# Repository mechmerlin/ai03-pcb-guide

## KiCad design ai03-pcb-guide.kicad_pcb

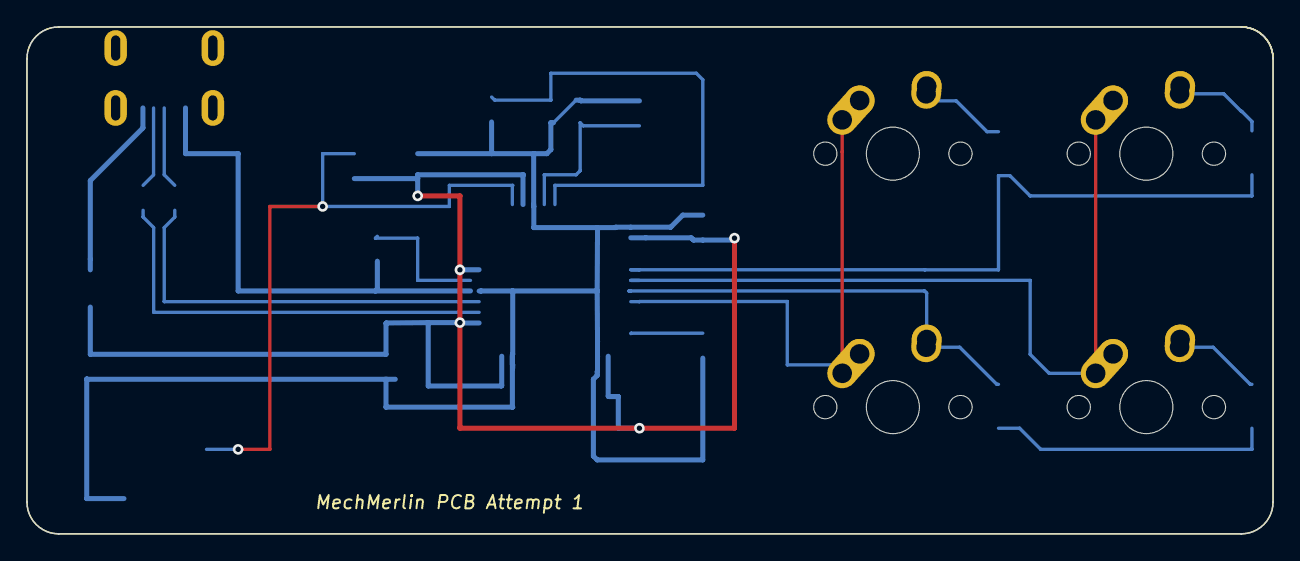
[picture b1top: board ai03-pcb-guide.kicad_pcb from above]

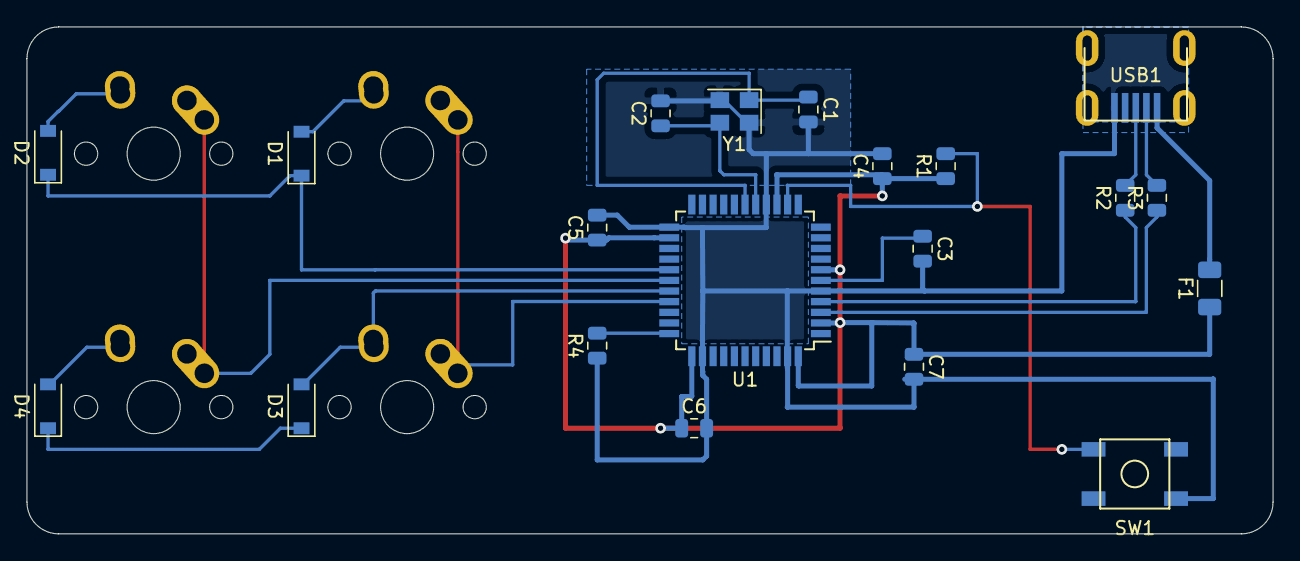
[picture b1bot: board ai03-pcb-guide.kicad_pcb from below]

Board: 2 copper layers, 93.7 x 38.1 mm, 24 parts (20 on the bottom side), 20 nets.

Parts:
C1, C2: 22pF; C_0805_2012Metric
C3: 1uF; C_0805_2012Metric
C4, C5, C6: 0.1uF; C_0805_2012Metric
C7: 10uF; C_0805_2012Metric
D1, D2, D3, D4: D_Small; D_SOD-123
F1: Polyfuse_Small; Fuse_1206_3216Metric
MX1, MX2, MX3, MX4: MX-NoLED; MX-1U-NoLED
R1, R4: 10k; R_0805_2012Metric
R2, R3: 22; R_0805_2012Metric
SW1: SW_Push; SKQG-1155865
U1: ATmega32U4-AU; TQFP-44_10x10mm_P0.8mm
USB1: Molex-0548190589
Y1: 16MHz; Crystal_SMD_3225-4Pin_3.2x2.5mm

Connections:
+5V: C4.1, C5.1, C6.1, C7.1, F1.1, R1.1, U1.2, U1.7, U1.14, U1.24, U1.34, U1.44
COL0: MX1.1, MX3.1, U1.30
COL1: MX2.1, MX4.1, U1.28
D+: R2.2, USB1.3
D-: R3.2, USB1.4
GND: C1.2, C2.2, C3.2, C4.2, C5.2, C6.2, C7.2, R4.1, SW1.1, U1.5, U1.15, U1.23, U1.35, U1.43, USB1.1, Y1.2, Y1.4
unnamed: C1.1, U1.17, Y1.1
unnamed: C2.1, U1.16, Y1.3
unnamed: C3.1, U1.6
unnamed: D1.2, MX1.2
unnamed: D2.2, MX2.2
unnamed: D3.1, D4.1
unnamed: D4.2, MX4.2
unnamed: R1.2, SW1.2, U1.13
unnamed: R2.1, U1.4
unnamed: R3.1, U1.3
unnamed: R4.2, U1.33
ROW0: D1.1, D2.1, U1.27
ROW1: D3.2, MX3.2, U1.29
VCC: F1.2, USB1.5

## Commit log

2019-12-12 add submodules
2019-12-12 add footprint libraries
2019-12-12 Part 3 MCU schematic done
2019-12-12 add in additional files
2019-12-12 add in the switch matrix and USB port schematic
2019-12-12 finish Step 7: Assigning Footprints
2019-12-14 get some pcb work done
2019-12-19 finished PCB
2019-12-19 fill zones
2019-12-19 add silkscreen
2019-12-26 add submodules for usb c
2019-12-26 add usb c to symbol library
2019-12-26 finish schematic
